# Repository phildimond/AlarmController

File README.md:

# AlarmController
 ESP32 Ethernet Alarm controller with MQTT integration

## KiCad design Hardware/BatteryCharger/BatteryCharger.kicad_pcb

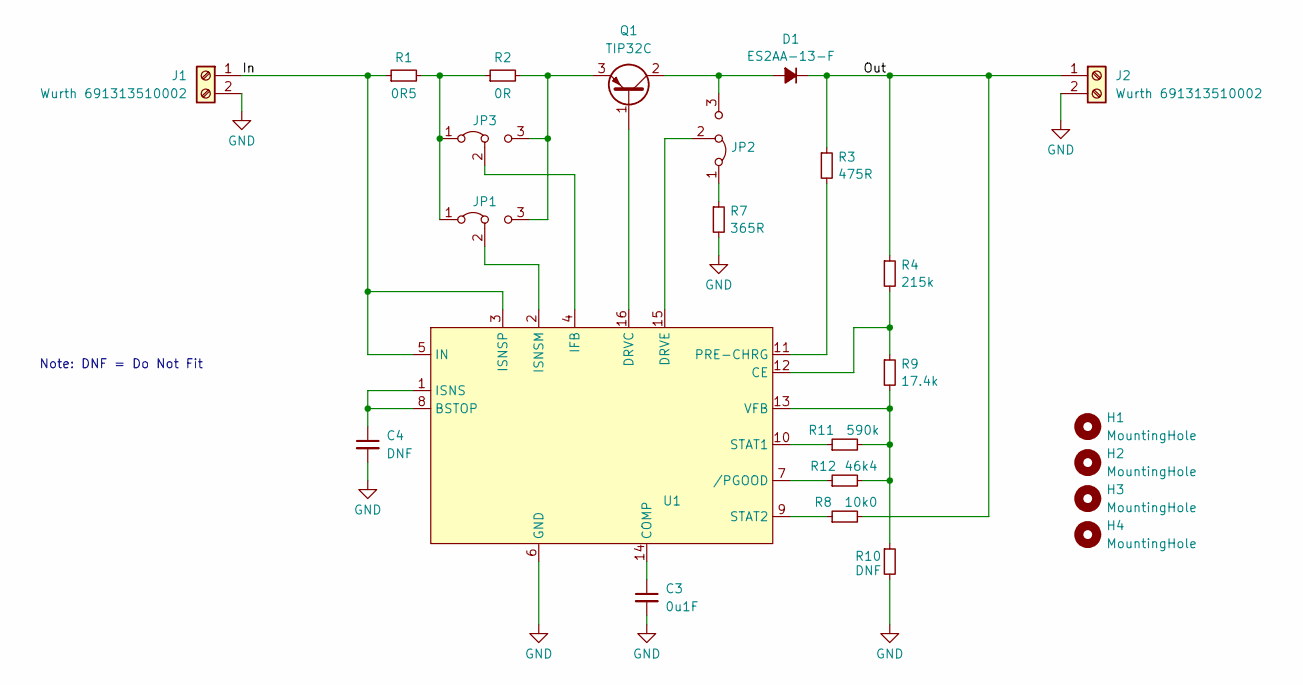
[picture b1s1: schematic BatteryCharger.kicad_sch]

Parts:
C3: 0u1F; C_Axial_L5.1mm_D3.1mm_P10.00mm_Horizontal
C4: DNF; C_Axial_L5.1mm_D3.1mm_P10.00mm_Horizontal
D1: ES2AA-13-F; D_SMA
H1, H2, H3, H4: MountingHole; MountingHole_3.2mm_M3
J1, J2: Wurth 691313510002; Wurth_691313510002_Pluggable_Terminal_Block
JP1, JP2, JP3: Jumper_3_Bridged12; SolderJumper-3_P1.3mm_Bridged12_Pad1.0x1.5mm
Q1: TIP32C; TO-220-3_Vertical
R1: 0R5; R_2512 Large Pad; Part CSRN2512FKR500
R2: 0R; R_Axial_DIN0207_L6.3mm_D2.5mm_P10.16mm_Horizontal; Part CSRN2512FKR500
R3: 475R; R_Axial_DIN0207_L6.3mm_D2.5mm_P10.16mm_Horizontal
R4: 215k; R_Axial_DIN0207_L6.3mm_D2.5mm_P10.16mm_Horizontal
R7: 365R; R_Axial_DIN0207_L6.3mm_D2.5mm_P10.16mm_Horizontal
R8: 10k0; R_Axial_DIN0207_L6.3mm_D2.5mm_P10.16mm_Horizontal
R9: 17.4k; R_Axial_DIN0207_L6.3mm_D2.5mm_P10.16mm_Horizontal
R10: DNF; R_Axial_DIN0207_L6.3mm_D2.5mm_P10.16mm_Horizontal
R11: 590k; R_Axial_DIN0207_L6.3mm_D2.5mm_P10.16mm_Horizontal
R12: 46k4; R_Axial_DIN0207_L6.3mm_D2.5mm_P10.16mm_Horizontal
U1: SOIC-16W_7.5x10.3mm_P1.27mm

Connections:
/In: J1.1, R1.1, U1.3 (ISNSP), U1.5 (IN)
/Out: D1.1 (K), J2.1, R3.1, R4.1, R8.2
GND: C3.2, C4.2, J1.2, J2.2, R7.2, R10.2, U1.6 (GND)
unnamed: D1.2 (A), JP2.3 (B), Q1.2 (C)
unnamed: JP1.1 (A), JP3.1 (A), R1.2, R2.1
unnamed: JP1.3 (B), JP3.3 (B), Q1.3 (E), R2.2
unnamed: JP1.2 (C), U1.2 (ISNSM)
unnamed: JP2.1 (A), R7.1
unnamed: JP2.2 (C), U1.15 (DRVE)
unnamed: JP3.2 (C), U1.4 (IFB)
unnamed: Q1.1 (B), U1.16 (DRVC)
unnamed: C4.1, U1.1 (ISNS), U1.8 (BSTOP)
unnamed: R4.2, R9.1, U1.12 (CE)
unnamed: C3.1, U1.14 (COMP)
unnamed: R3.2, U1.11 (PRE-CHRG)
unnamed: R11.1, U1.10 (STAT1)
unnamed: R8.1, U1.9 (STAT2)
unnamed: R9.2, R10.1, R11.2, R12.2, U1.13 (VFB)
unnamed: R12.1, U1.7 (/PGOOD)

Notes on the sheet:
Note: DNF = Do Not Fit

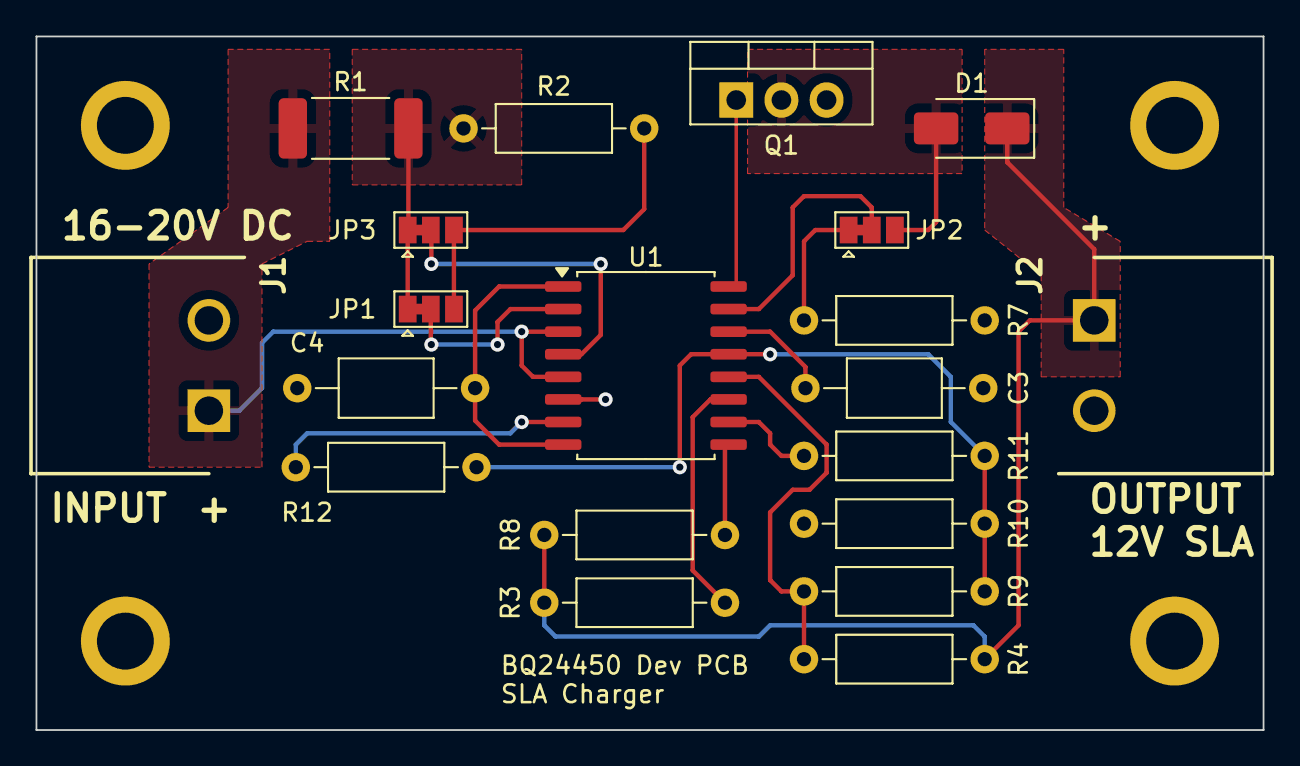
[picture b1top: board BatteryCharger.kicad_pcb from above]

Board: 2 copper layers, 69.0 x 39.0 mm, 24 parts (0 on the bottom side), 19 nets.

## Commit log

2024-01-27 Events working, array of input configs added
2024-01-27 Started adding input code
2024-01-29 Moved Ethernet operations to separate files
2024-02-04 Added input debounce, refactored input code
2024-02-05 Added some hardware notes
2024-02-07 Added state messaging via MQTT
2024-02-24 Added datasheets. Lost a lot of work when PC drive died!
2024-02-28 Working on the charger schematic
2024-02-29 Progress Check-in, working on schematic
2024-02-29 Progress check-in: working on charger schematic
2024-02-29 Progress: Finished schematic, starting on PCB
2024-03-01 Progress - Laying out PCB
2024-03-01 Initial PCB layout for charger
2024-03-01 Board layout done, ready to check
2024-03-02 Fix error on charger PCB and add mounting holes to schematic
2024-03-03 Charger: Minor PCB cleanup & generate manufacturing files
2024-03-05 Ready to deploy
    Minor fixes, set all inputs to NC
2024-03-17 Start Alarm unit layout
2024-04-03 Working on hardware design to add outputs
2024-04-18 Updated power circuits on alarm schematic
2024-05-04 Schematic Update
2024-05-18 Updated .gitignore
2024-05-18 Another .gitignore change
2024-05-19 Revert "Delete build directory"
    This reverts commit 51411854c77ccb16800c0e6f65b8999cf7ea8898.
2024-05-22 Working on outputs
2024-05-26 Minor schematic changes
2024-05-26 Changes to not care about ethernet and mqtt status on startup
2024-05-27 Added alarm machine and started coding it
2024-05-27 Added host control of siren outputs
2024-05-27 Siren commands from host & state reflection working
2024-05-29 Working on the alarm machine
2024-05-30 Update schematic with CPU pins to connectors
